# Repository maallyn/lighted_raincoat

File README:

This repository contains the design for my project
to create a computer controlled animated lighted
clear plastic raincoat as a challenge in hardware
design, software design, sewing, and of course art.

Anyone is welcome to use this software and hardware
design

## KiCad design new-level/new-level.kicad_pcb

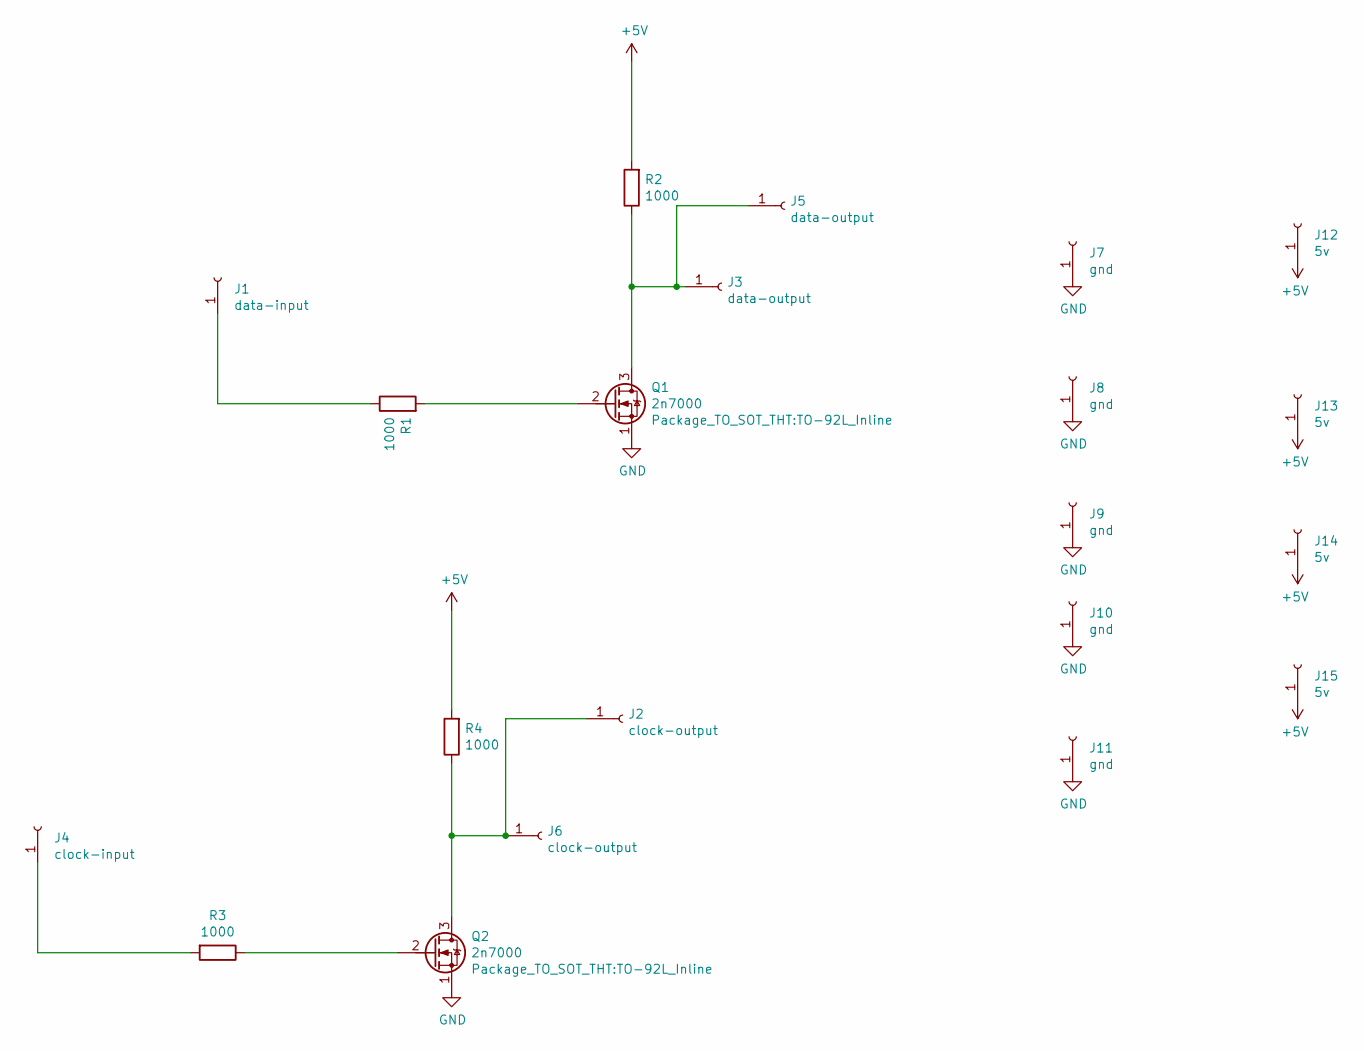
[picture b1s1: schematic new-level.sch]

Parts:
J1: data-input; SolderWire-0.5sqmm_1x01_D0.9mm_OD2.1mm
J2, J6: clock-output; SolderWire-0.5sqmm_1x01_D0.9mm_OD2.1mm
J3, J5: data-output; SolderWire-0.5sqmm_1x01_D0.9mm_OD2.1mm
J4: clock-input; SolderWire-0.5sqmm_1x01_D0.9mm_OD2.1mm
J7, J8, J9, J10, J11: gnd; SolderWire-0.5sqmm_1x01_D0.9mm_OD2.1mm
J12, J13, J14, J15: 5v; SolderWire-0.5sqmm_1x01_D0.9mm_OD2.1mm
Q1, Q2: 2n7000; TO-92L_Inline
R1, R2, R3, R4: 1000; R_Axial_DIN0207_L6.3mm_D2.5mm_P10.16mm_Horizontal

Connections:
+5V: J12.1, J13.1, J14.1, J15.1, R2.2, R4.2
GND: J7.1, J8.1, J9.1, J10.1, J11.1, Q1.1 (S), Q2.1 (S)
unnamed: J1.1, R1.1
unnamed: J2.1, J6.1, Q2.3 (D), R4.1
unnamed: J3.1, J5.1, Q1.3 (D), R2.1
unnamed: J4.1, R3.2
unnamed: Q1.2 (G), R1.2
unnamed: Q2.2 (G), R3.1

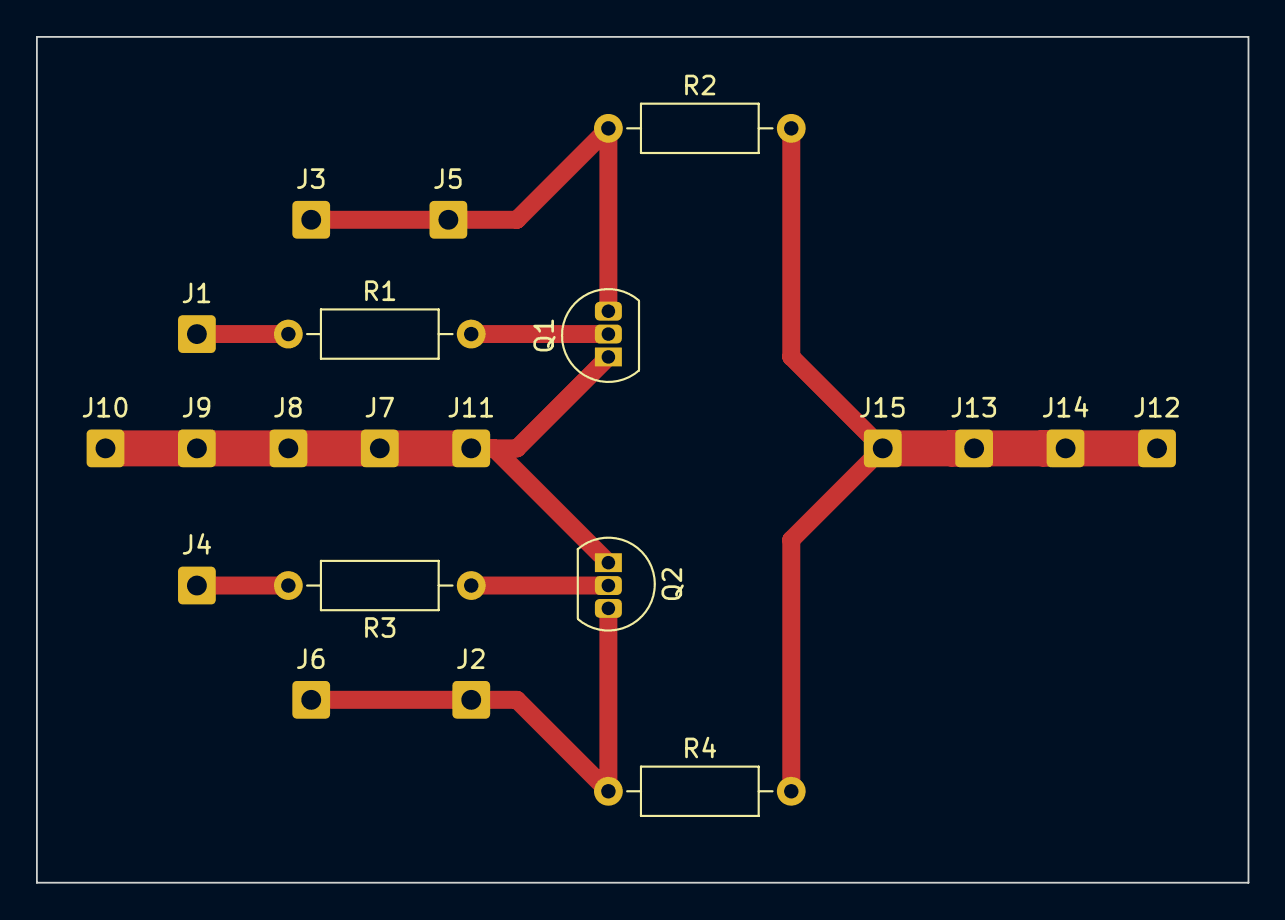
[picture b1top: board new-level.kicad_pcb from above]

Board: 2 copper layers, 67.3 x 47.0 mm, 21 parts (0 on the bottom side), 8 nets.

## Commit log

2020-11-02 Initial commit with level changer circuit
2020-11-02 This is the initial commit for the hardware design files for the logic level converter for the Raspberry PI to LED Strip data
2020-11-11 Made my first test progrm and made my first Makefile
2020-12-08 Begin high speed testing
2020-12-08 Completed function to output a byte to the LED Strip Each bit is 10 us long; clock upswings in the center of each 10 us bit.
2020-12-10 Add functions to send start, end, and led values to the LED strip
2020-12-11 Add structures and started work on allocation functions
2020-12-15 Set up arrays for strips, led strings and logical led strings Changed send byte to take advantage of array of strips
2020-12-16 Continue to work on logical to physical strip transfer
2020-12-16 Renamed c file to cpp file for C++
2020-12-17 Initial xml file
2020-12-17 Complete first version XML file
2021-01-04 Periodic commit; updating Makefile for C++ and XML description file
2021-01-07 Change from xml to yaml
2021-01-11 Complete first revision of yaml file
2021-01-11 Fix Makefile to link yaml and add yaml init in main program
2021-01-11 Still learning yaml library
2021-01-13 Correct blocking in yaml file
2021-04-01 periodic checkin
2021-04-02 updated setup to use strip structure
2021-04-02 Add null checks
2021-04-05 Add enumeration for yaml parsing
2021-04-06 Start working on parsing and setting up physical & logical strings
2021-04-08 Change name to proper attribute
2021-04-09 Add strip to physical string Made corrections to yaml file
2021-04-09 Add strip information in yaml file Add memory allocation/initialization for strip, physical, logical, and led data types
2021-04-10 Working on parsing; now at figuring keys tokens
2021-04-15 Remove yaml file and processing - will use simple config file
2021-04-15 Implementing simple config file parsing
2021-04-16 Continue to work on configuration - completed item count and memory allocation
2021-04-16 Need to allocate for two sets of logical strings for each physical string for current and next set of strings
2021-04-16 Get rid of strip data type; gpio is now in physical strings
2021-04-17 Continue parsing garment sections; working on led strings
2021-04-17 Worked on physical string led count & pointer
2021-04-18 Complete counting of logical leds; elimination of backup logical string
2021-04-20 Initial commit of separated files from original test_program
2021-09-10 Remove comment about dual logical strings
2021-09-11 Removing more comments for multiple logical strings
2021-09-12 testing array population
2021-09-13 Make changes to the production code; I accidently updated the original test code which is now legacy.
2021-09-14 Debugging logical array setup
2021-09-14 Continue testing; adding some basic test code
2021-09-15 Working on testing
2022-02-11 Remove yaml; not needed
2022-03-19 Initial config file on backup; using new config file for initial testing
2022-03-19 Preparing to do preliminary testing
2022-03-19 Initial testing with leds
2022-03-20 Add from and to led strings for transitioning
2022-03-22 Added some variables related to transitions
2022-03-22 Working on low level code for fading
